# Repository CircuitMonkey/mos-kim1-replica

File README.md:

# mos-kim1-replica
MOS KIM-1 6502 replica project using CHIPz modules.

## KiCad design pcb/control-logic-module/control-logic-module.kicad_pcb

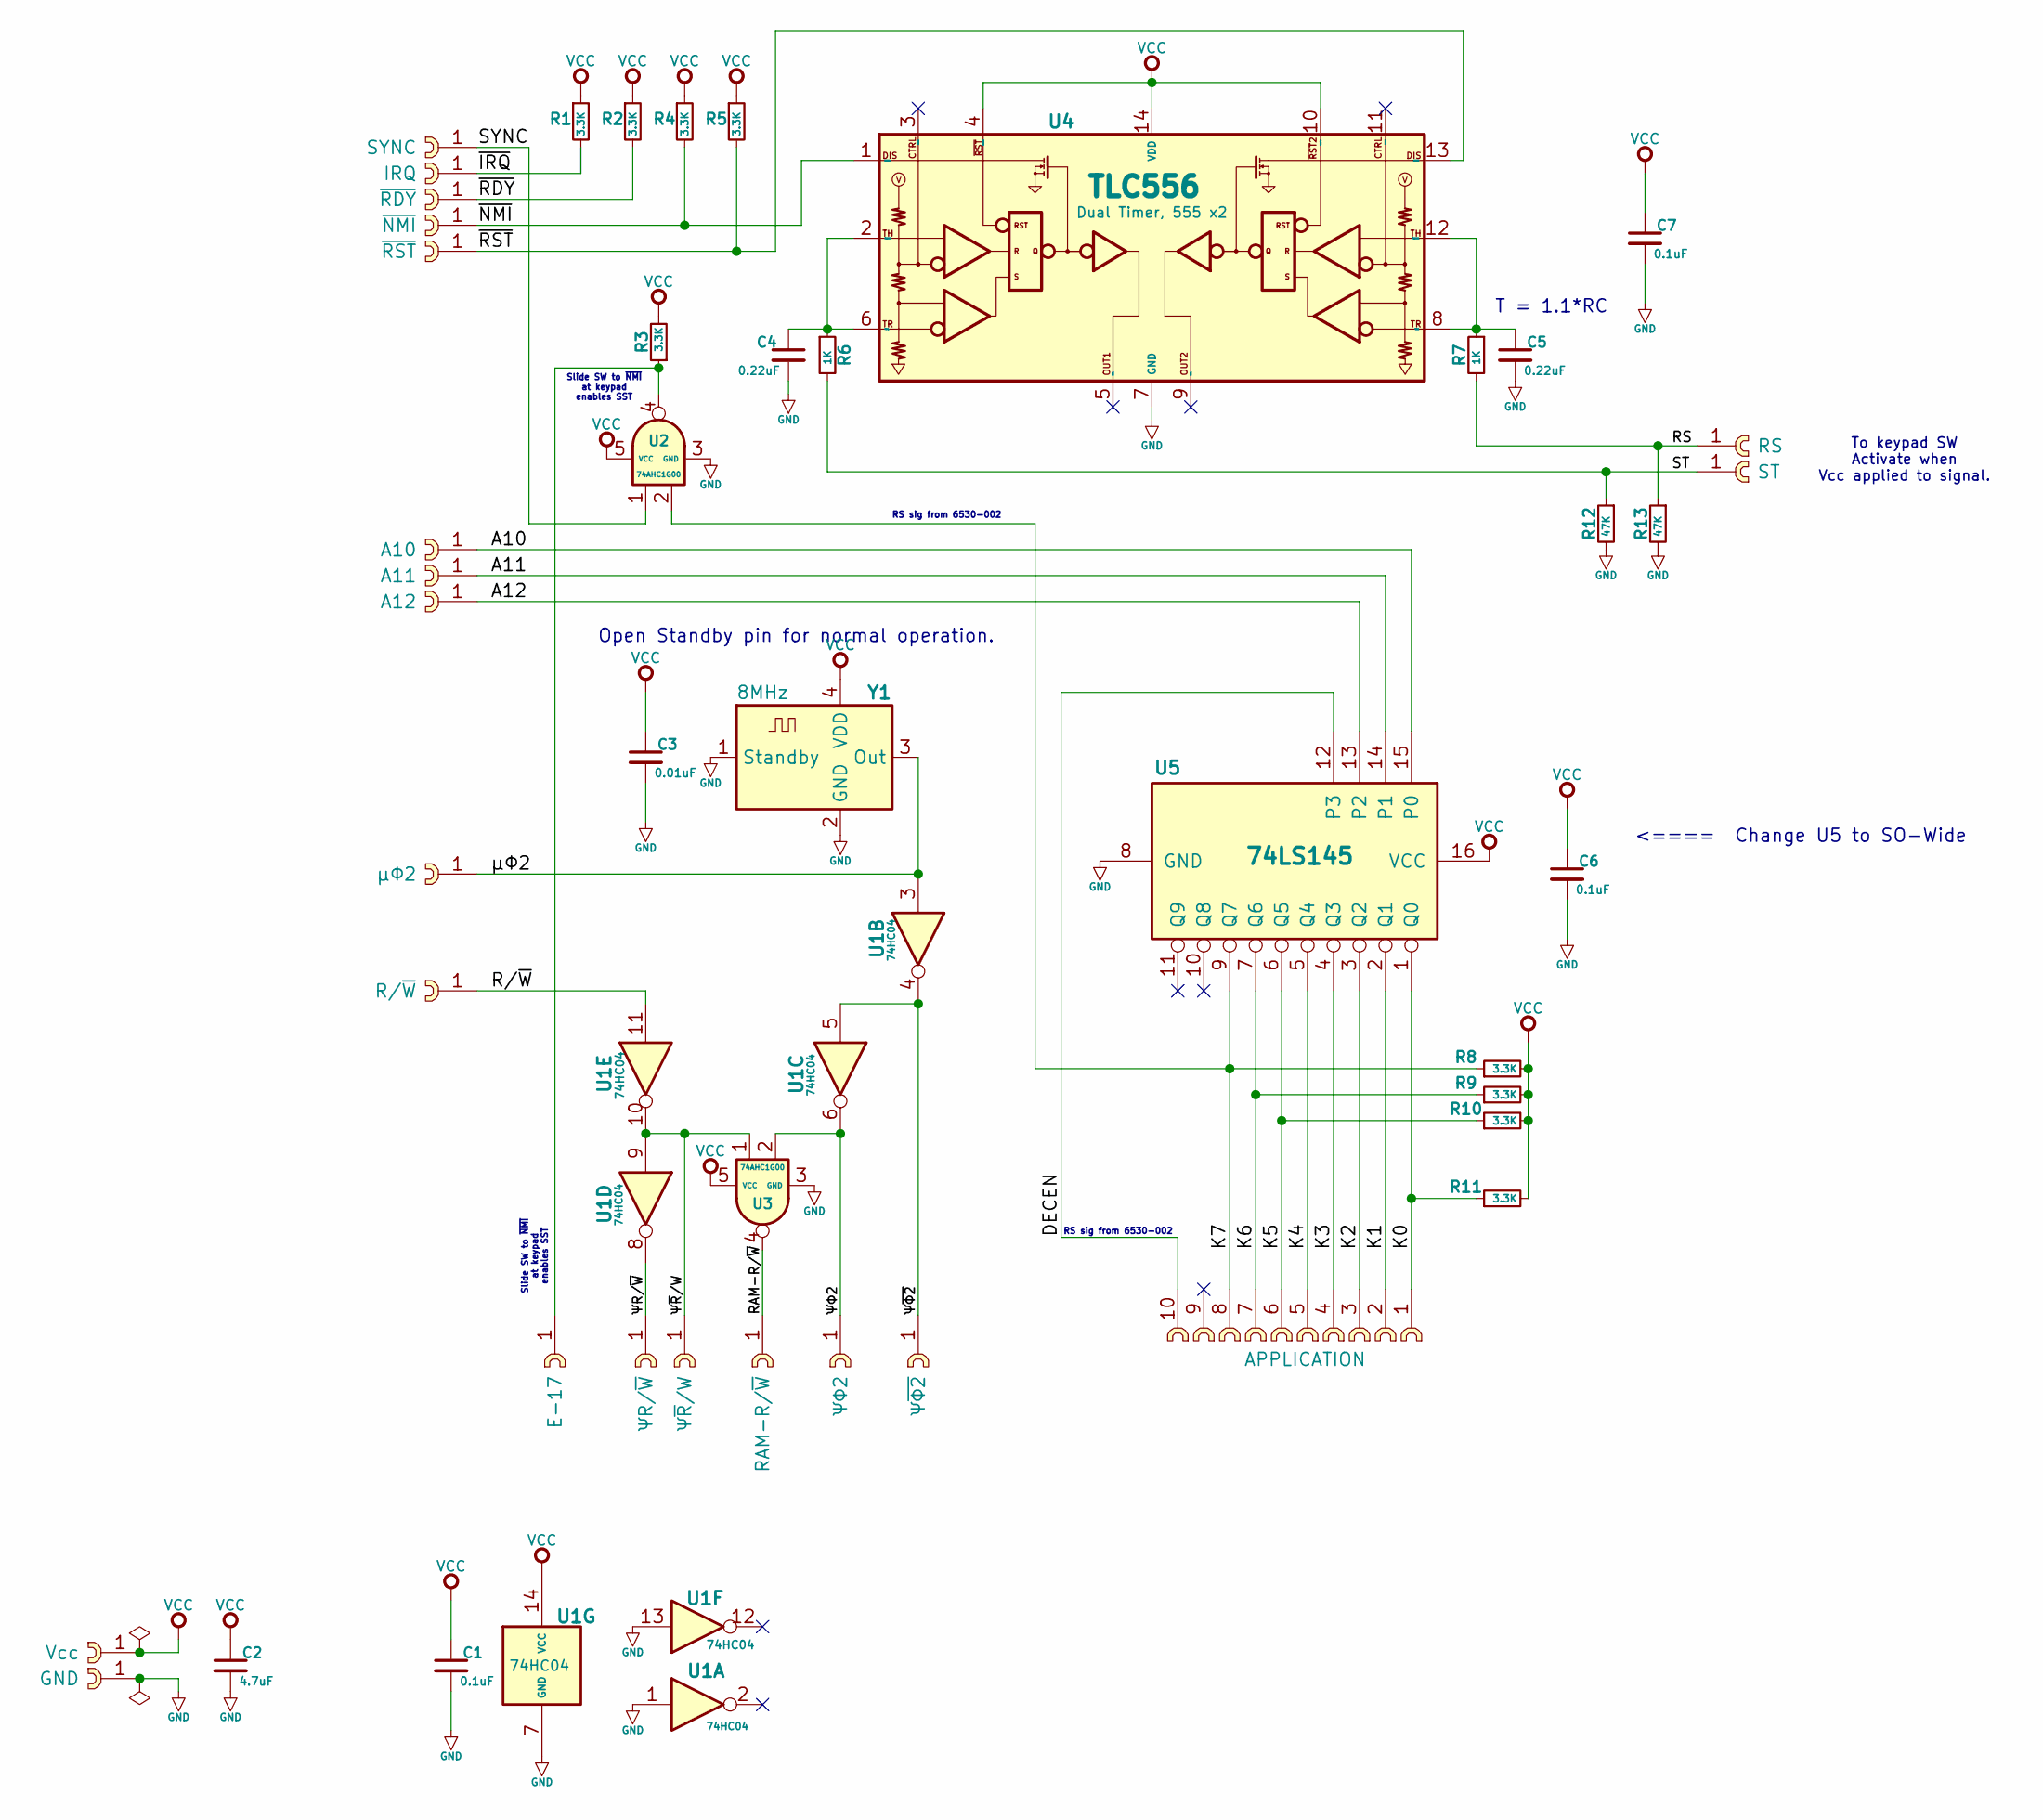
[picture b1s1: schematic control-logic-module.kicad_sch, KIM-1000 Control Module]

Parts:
C1, C6, C7: 0.1uF; C_0603_1608Metric
C2: 4.7uF; C_0603_1608Metric
C3: 0.01uF; C_0603_1608Metric
C4, C5: 0.22uF; C_0603_1608Metric
CST1: Vcc; cast-2.0-01P
CST2: GND; cast-2.0-01P
CST3: SYNC; cast-2.0-01P
CST4: IRQ; cast-2.0-01P
CST5: ~{RDY}; cast-2.0-01P
CST6: ~{NMI}; cast-2.0-01P
CST7: ~{RST}; cast-2.0-01P
CST8: A10; cast-2.0-01P
CST9: A11; cast-2.0-01P
CST10: A12; cast-2.0-01P
CST11: μΦ2; cast-2.0-01P
CST12: R/~{W}; cast-2.0-01P
CST13: E-17; cast-2.0-01P
CST14: ΨR/~{W}; cast-2.0-01P
CST15: Ψ~{R}/W; cast-2.0-01P
CST16: RAM-R/~{W}; cast-2.0-01P
CST17: ΨΦ2; cast-2.0-01P
CST18: Ψ~{Φ2}; cast-2.0-01P
CST19: APPLICATION; cast-2.0-10P
CST20: RS; cast-2.0-01P
CST21: ST; cast-2.0-01P
R1, R2, R3, R4, R5, R8, R9, R10, R11: 3.3K; R_0603_1608Metric
R6, R7: 1K; R_0603_1608Metric
R12, R13: 47K; R_0603_1608Metric
U1: 74HC04; QFN-14_EP_2.5x3_Pitch0.5mm
U2, U3: 74AHC1G00; SOT-353_SC-70-5; MPN MC74HC1G00DFT1G
U4: TLC556; SO-14_3.9x8.65mm_P1.27mm
U5: 74LS145; SO-16_3.9x9.9mm_P1.27mm
Y1: 8MHz; Oscillator_SMD_Abracon_ASDMB-4Pin_2.5x2.0mm; MPN ASD-8.000MHZ-LC-T

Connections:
/A10: CST8.1, U5.15 (P0)
/A11: CST9.1, U5.14 (P1)
/A12: CST10.1, U5.13 (P2)
/DECEN: CST19.10, U5.12 (P3)
/K0: CST19.1, R11.1, U5.1 (Q0)
/K1: CST19.2, U5.2 (Q1)
/K2: CST19.3, U5.3 (Q2)
/K3: CST19.4, U5.4 (Q3)
/K4: CST19.5, U5.5 (Q4)
/K5: CST19.6, R10.1, U5.6 (Q5)
/K6: CST19.7, R9.1, U5.7 (Q6)
/K7: CST19.8, R8.1, U2.2, U5.9 (Q7)
/RAM-R/~W: CST16.1, U3.4
/RS: CST20.1, R7.2, R13.1
/R/~W: CST12.1, U1.11
/ST: CST21.1, R6.2, R12.1
/SYNC: CST3.1, U2.1
/~IRQ: CST4.1, R1.2
/~NMI: CST6.1, R4.2, U4.1 (DISCH1)
/~RDY: CST5.1, R2.2
/~RST: CST7.1, R5.2, U4.13 (DISCH2)
/ΨR/~W: CST14.1, U1.8
/Ψ~R/W: CST15.1, U1.9, U1.10, U3.1
/Ψ~Φ2: CST18.1, U1.4, U1.5
/ΨΦ2: CST17.1, U1.6, U3.2
/μΦ2: CST11.1, U1.3, Y1.3 (Out)
GND: C1.2, C2.2, C3.2, C4.2, C5.2, C6.2, C7.2, CST2.1, R12.2, R13.2, U1.1, U1.7 (GND), U1.13, U2.3 (GND), U3.3 (GND), U4.7 (GND), U5.8 (GND), Y1.1 (Standby), Y1.2 (GND)
unnamed: CST13.1, R3.1, U2.4
unnamed: C4.1, R6.1, U4.2 (THRESH1), U4.6 (TRIG1)
unnamed: C5.1, R7.1, U4.8 (TRIG2), U4.12 (THRESH2)
VCC: C1.1, C2.1, C3.1, C6.1, C7.1, CST1.1, R1.1, R2.1, R3.2, R4.1, R5.1, R8.2, R9.2, R10.2, R11.2, U1.14 (VCC), U2.5 (VCC), U3.5 (VCC), U4.4 (RESET1), U4.10 (RESET2), U4.14 (VDD), U5.16 (VCC), Y1.4 (VDD)

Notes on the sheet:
RS sig from 6530-002
Slide SW to ~{NMI} at keypad enables SST
T = 1.1*RC
Open Standby pin for normal operation.
To keypad SW Activate when Vcc applied to signal.
<==== Change U5 to SO-Wide

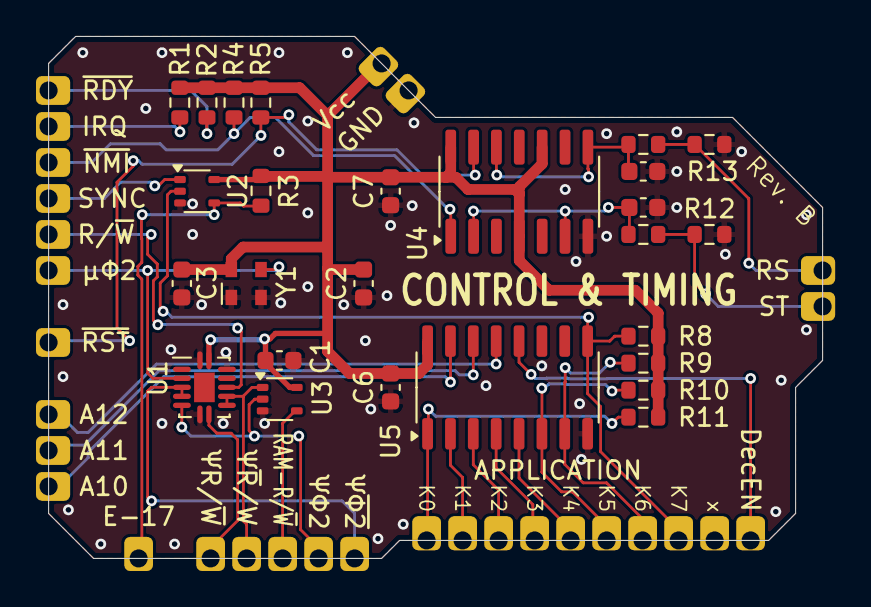
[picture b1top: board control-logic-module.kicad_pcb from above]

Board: 2 copper layers, 43.0 x 29.0 mm, 47 parts (0 on the bottom side), 31 nets.

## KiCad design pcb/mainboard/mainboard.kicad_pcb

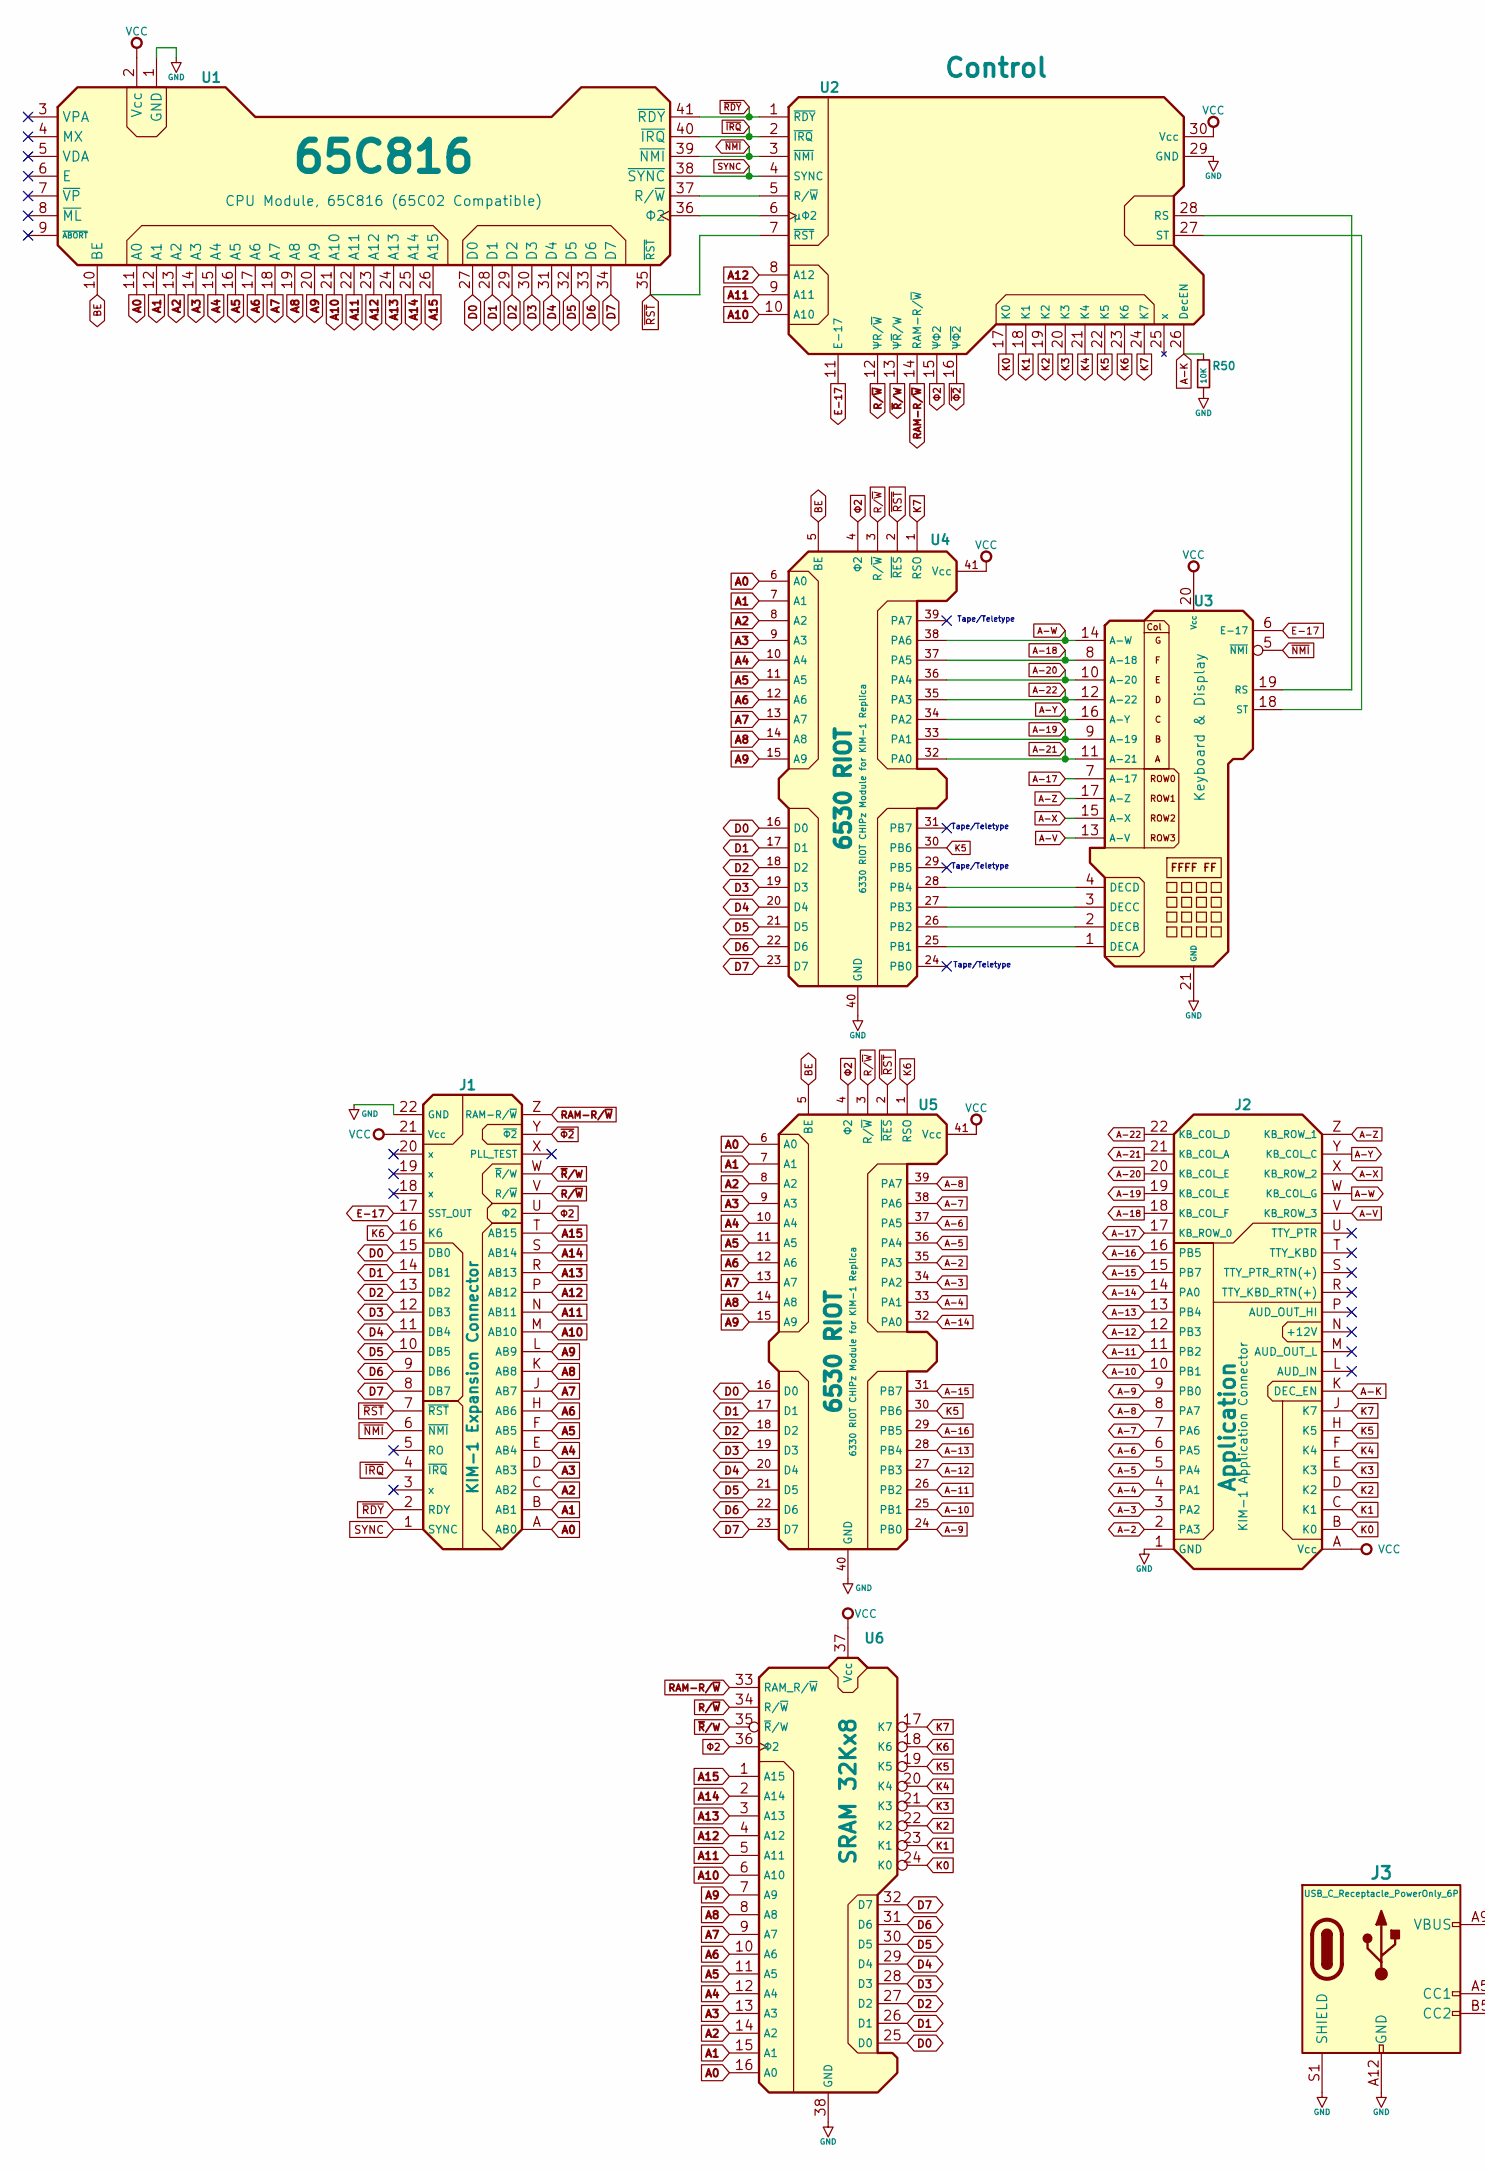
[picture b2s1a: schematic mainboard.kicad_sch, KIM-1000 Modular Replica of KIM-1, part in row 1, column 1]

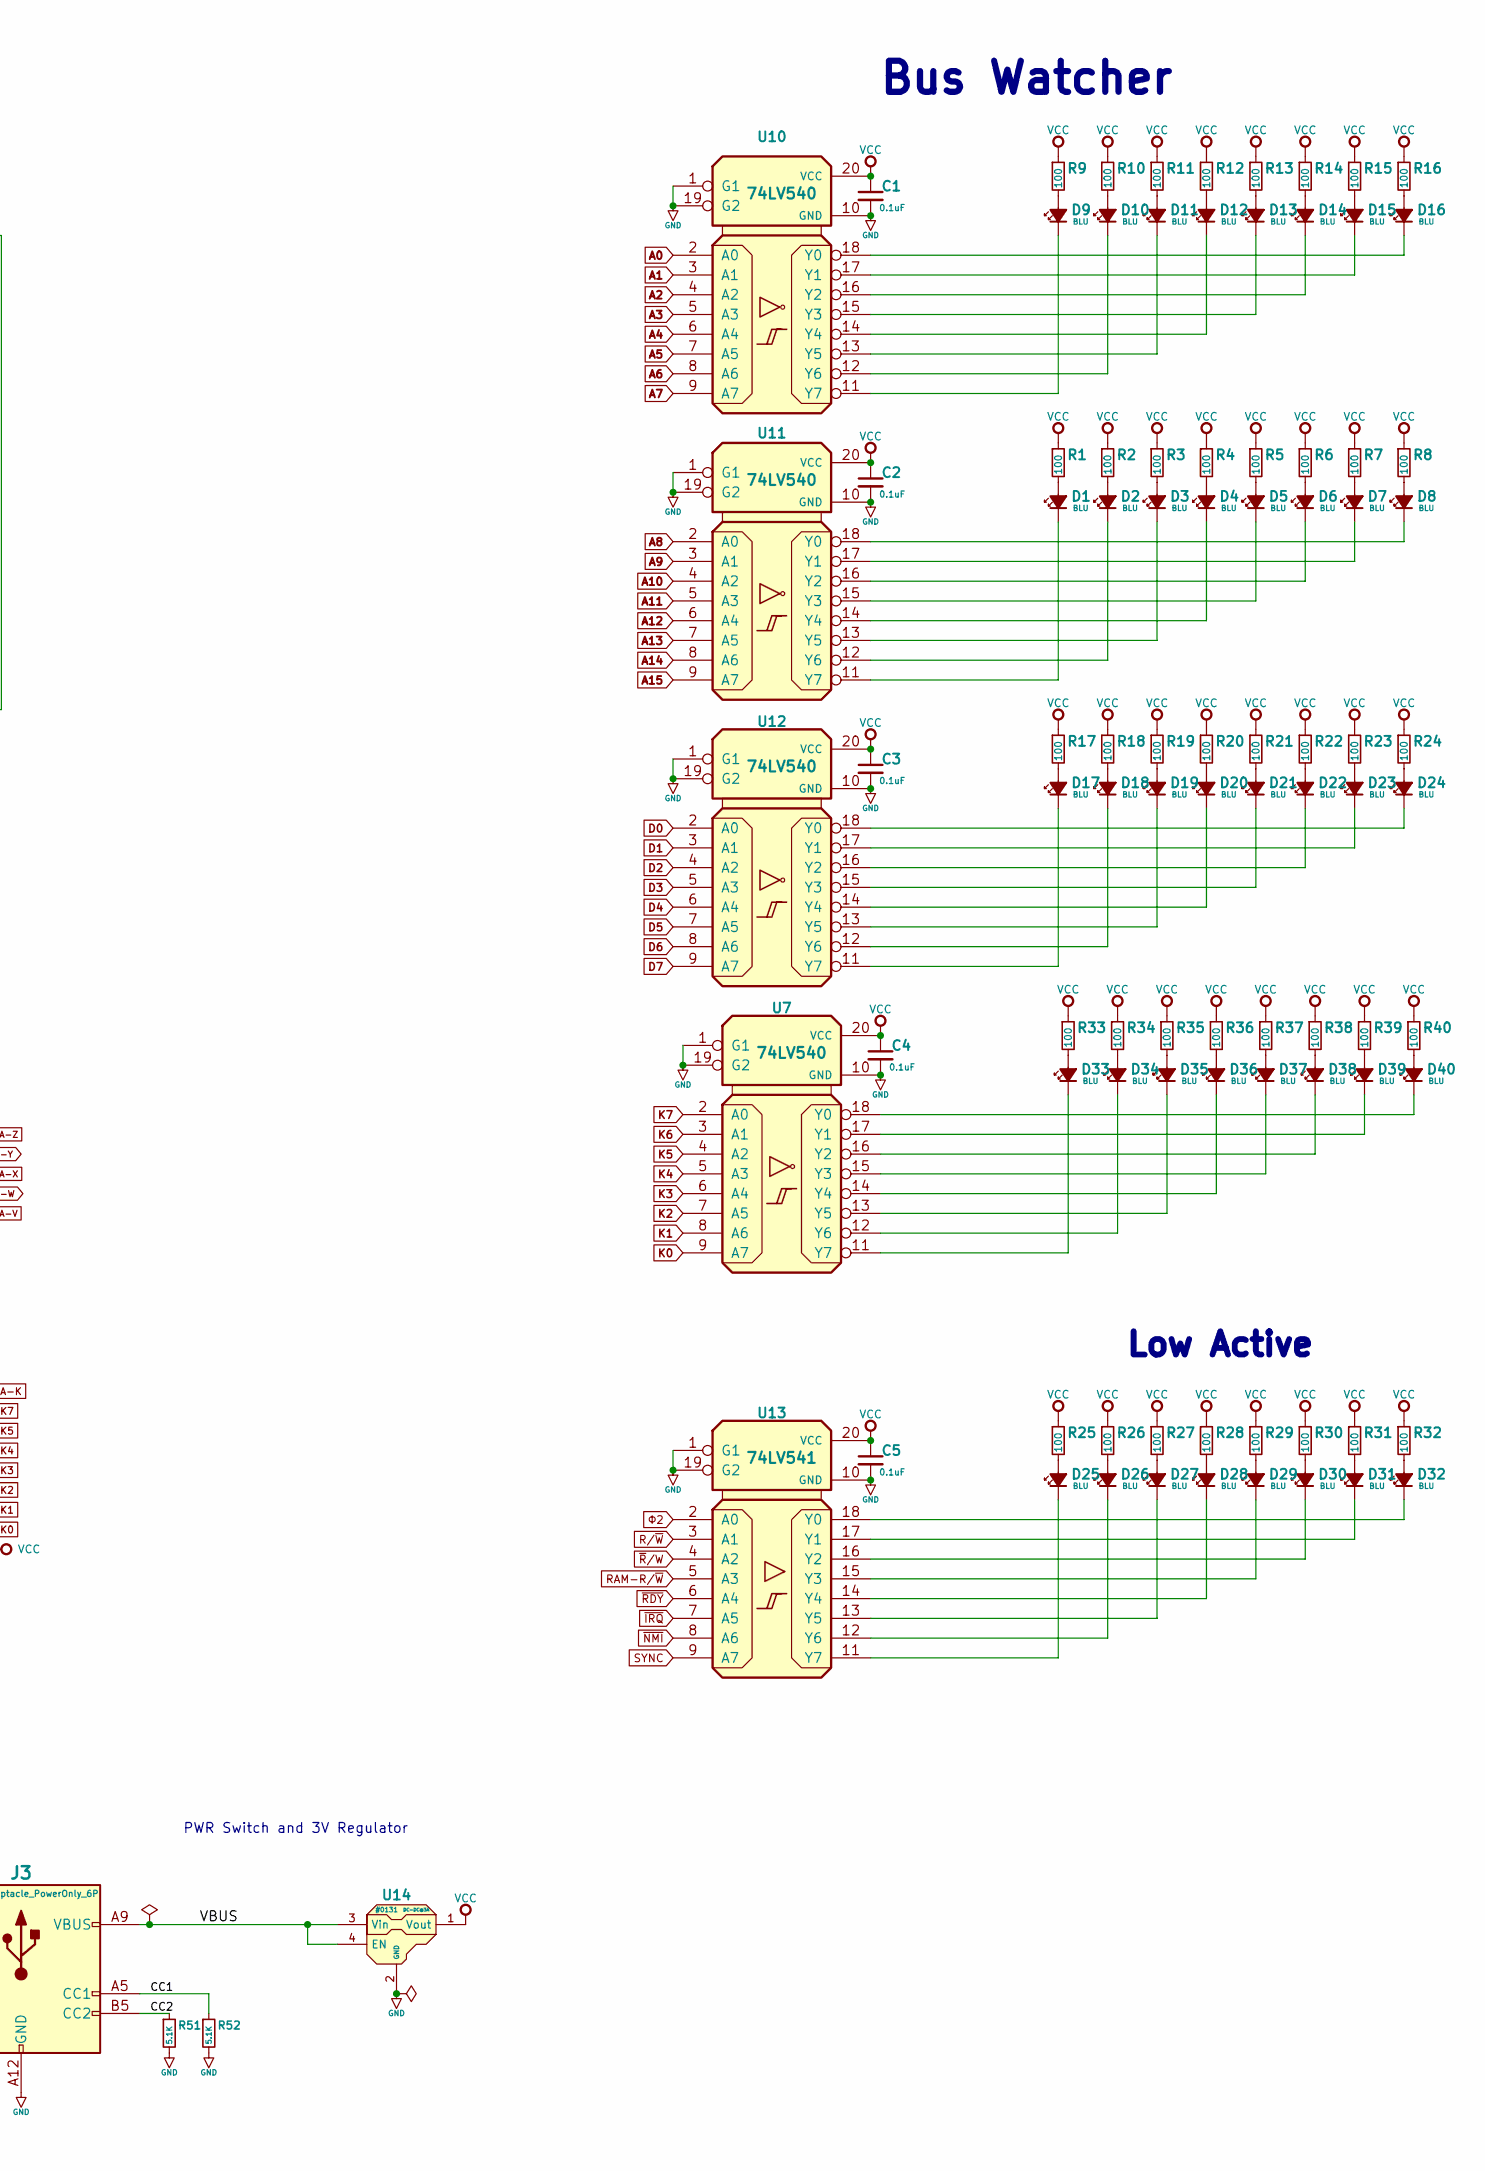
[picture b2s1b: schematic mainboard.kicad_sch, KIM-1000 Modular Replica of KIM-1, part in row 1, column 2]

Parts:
C1, C2, C3, C4, C5: 0.1uF; C_0603_1608Metric
D1, D2, D3, D4, D5, D6, D7, D8, D9, D10, D11, D12, D13, D14, D15, D16, D17, D18, D19, D20, D21, D22, D23, D24, D25, D26, D27, D28, D29, D30, D31, D32, D33, D34, D35, D36, D37, D38, D39, D40: BLU; LED_0603_1608Metric
J1: Expansion
J2: Application; Expansion
J3: USB_C_Receptacle_PowerOnly_6P; USB_C_Receptacle_HRO_TYPE-C-31-M-17
R1, R2, R3, R4, R5, R6, R7, R8, R9, R10, R11, R12, R13, R14, R15, R16, R17, R18, R19, R20, R21, R22, R23, R24, R25, R26, R27, R28, R29, R30, R31, R32, R33, R34, R35, R36, R37, R38, R39, R40: 100; R_0603_1608Metric
R50: 10K; R_0603_1608Metric
R51, R52: 5.1K; R_0603_1608Metric
U1: 65C816; CPU_65C816_Module
U2: Control; KIM1-Control-CHIPz-Module
U3: Keyboard & Display; KIM1-Kbd-Display-Module
U4, U5: 6530 RIOT; IO_6530_RIOT
U6: SRAM 32Kx8; KIM1-CHIPz-SRAM-32Kx8
U7, U10, U11, U12: 74LV540; TI_RGY0020A-VQFN-20-Pad_3.5x4.5mm; MPN SN74LV540ARGY
U13: 74LV541; TI_RKS0020B-VQFN-20-Pad_2.5x4.5mm; MPN SN74LV540ARGY
U14: #0131; 0131-DC-DC-3A

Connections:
/CC1: J3.A5 (CC1), R52.1
/CC2: J3.B5 (CC2), R51.1
/VBUS: J3.A9 (VBUS), J3.B9 (VBUS), U14.3 (Vin), U14.4 (EN)
A0: J1.A (AB0), U1.11 (A0), U4.6 (A0), U5.6 (A0), U6.16 (A0), U10.2 (A0)
A1: J1.B (AB1), U1.12 (A1), U4.7 (A1), U5.7 (A1), U6.15 (A1), U10.3 (A1)
A2: J1.C (AB2), U1.13 (A2), U4.8 (A2), U5.8 (A2), U6.14 (A2), U10.4 (A2)
A3: J1.D (AB3), U1.14 (A3), U4.9 (A3), U5.9 (A3), U6.13 (A3), U10.5 (A3)
A4: J1.E (AB4), U1.15 (A4), U4.10 (A4), U5.10 (A4), U6.12 (A4), U10.6 (A4)
A5: J1.F (AB5), U1.16 (A5), U4.11 (A5), U5.11 (A5), U6.11 (A5), U10.7 (A5)
A6: J1.H (AB6), U1.17 (A6), U4.12 (A6), U5.12 (A6), U6.10 (A6), U10.8 (A6)
A7: J1.J (AB7), U1.18 (A7), U4.13 (A7), U5.13 (A7), U6.9 (A7), U10.9 (A7)
A8: J1.K (AB8), U1.19 (A8), U4.14 (A8), U5.14 (A8), U6.8 (A8), U11.2 (A0)
A9: J1.L (AB9), U1.20 (A9), U4.15 (A9), U5.15 (A9), U6.7 (A9), U11.3 (A1)
A10: J1.M (AB10), U1.21 (A10), U2.10 (A10), U6.6 (A10), U11.4 (A2)
A11: J1.N (AB11), U1.22 (A11), U2.9 (A11), U6.5 (A11), U11.5 (A3)
A12: J1.P (AB12), U1.23 (A12), U2.8 (A12), U6.4 (A12), U11.6 (A4)
A13: J1.R (AB13), U1.24 (A13), U6.3 (A13), U11.7 (A5)
A14: J1.S (AB14), U1.25 (A14), U6.2 (A14), U11.8 (A6)
A15: J1.T (AB15), U1.26 (A15), U6.1 (A15), U11.9 (A7)
A-2: J2.2 (PA3), U5.35 (PA3)
A-3: J2.3 (PA2), U5.34 (PA2)
A-4: J2.4 (PA1), U5.33 (PA1)
A-5: J2.5 (PA4), U5.36 (PA4)
A-6: J2.6 (PA5), U5.37 (PA5)
A-7: J2.7 (PA6), U5.38 (PA6)
A-8: J2.8 (PA7), U5.39 (PA7)
A-9: J2.9 (PB0), U5.24 (PB0)
A-10: J2.10 (PB1), U5.25 (PB1)
A-11: J2.11 (PB2), U5.26 (PB2)
A-12: J2.12 (PB3), U5.27 (PB3)
A-13: J2.13 (PB4), U5.28 (PB4)
A-14: J2.14 (PA0), U5.32 (PA0)
A-15: J2.15 (PB7), U5.31 (PB7)
A-16: J2.16 (PB5), U5.29 (PB5)
A-17: J2.17 (KB_ROW_0), U3.7 (A-17)
A-18: J2.18 (KB_COL_F), U3.8 (A-18), U4.37 (PA5)
A-19: J2.19 (KB_COL_E), U3.9 (A-19), U4.33 (PA1)
A-20: J2.20 (KB_COL_E), U3.10 (A-20), U4.36 (PA4)
A-21: J2.21 (KB_COL_A), U3.11 (A-21), U4.32 (PA0)
A-22: J2.22 (KB_COL_D), U3.12 (A-22), U4.35 (PA3)
A-K: J2.K (DEC_EN), R50.1, U2.26 (DecEN)
A-V: J2.V (KB_ROW_3), U3.13 (A-V)
A-W: J2.W (KB_COL_G), U3.14 (A-W), U4.38 (PA6)
A-X: J2.X (KB_ROW_2), U3.15 (A-X)
A-Y: J2.Y (KB_COL_C), U3.16 (A-Y), U4.34 (PA2)
A-Z: J2.Z (KB_ROW_1), U3.17 (A-Z)
BE: U1.10 (BE), U4.5 (BE), U5.5 (BE)
D0: J1.15 (DB0), U1.27 (D0), U4.16 (D0), U5.16 (D0), U6.25 (D0), U12.2 (A0)
D1: J1.14 (DB1), U1.28 (D1), U4.17 (D1), U5.17 (D1), U6.26 (D1), U12.3 (A1)
D2: J1.13 (DB2), U1.29 (D2), U4.18 (D2), U5.18 (D2), U6.27 (D2), U12.4 (A2)
D3: J1.12 (DB3), U1.30 (D3), U4.19 (D3), U5.19 (D3), U6.28 (D3), U12.5 (A3)
D4: J1.11 (DB4), U1.31 (D4), U4.20 (D4), U5.20 (D4), U6.29 (D4), U12.6 (A4)
D5: J1.10 (DB5), U1.32 (D5), U4.21 (D5), U5.21 (D5), U6.30 (D5), U12.7 (A5)
D6: J1.9 (DB6), U1.33 (D6), U4.22 (D6), U5.22 (D6), U6.31 (D6), U12.8 (A6)
D7: J1.8 (DB7), U1.34 (D7), U4.23 (D7), U5.23 (D7), U6.32 (D7), U12.9 (A7)
E-17: J1.17 (SST_OUT), U2.11 (E-17), U3.6 (E-17)
GND: C1.2, C2.2, C3.2, C4.2, C5.2, J1.22 (GND), J2.1 (GND), J3.A12 (GND), J3.B12 (GND), J3.S1 (SHIELD), R50.2, R51.2, R52.2, U1.1 (GND), U2.29 (GND), U3.21 (GND), U4.40 (GND), U5.40 (GND), U6.38 (GND), U7.1 (G1), U7.10 (GND), U7.19 (G2), U7.21 (GND), U10.1 (G1), U10.10 (GND), U10.19 (G2), U10.21 (GND), U11.1 (G1), U11.10 (GND), U11.19 (G2), U11.21 (GND), U12.1 (G1), U12.10 (GND), U12.19 (G2), U12.21 (GND), U13.1 (G1), U13.10 (GND), U13.19 (G2), U13.21 (GND), U14.2 (GND)
K0: J2.B (K0), U2.17 (K0), U6.24 (K0), U7.9 (A7)
K1: J2.C (K1), U2.18 (K1), U6.23 (K1), U7.8 (A6)
K2: J2.D (K2), U2.19 (K2), U6.22 (K2), U7.7 (A5)
K3: J2.E (K3), U2.20 (K3), U6.21 (K3), U7.6 (A4)
K4: J2.F (K4), U2.21 (K4), U6.20 (K4), U7.5 (A3)
K5: J2.H (K5), U2.22 (K5), U4.30 (PB6), U5.30 (PB6), U6.19 (K5), U7.4 (A2)
K6: J1.16 (K6), U2.23 (K6), U5.1 (RSO), U6.18 (K6), U7.3 (A1)
K7: J2.J (K7), U2.24 (K7), U4.1 (RSO), U6.17 (K7), U7.2 (A0)
unnamed: D1.2 (A), R1.2
unnamed: D1.1 (K), U11.11 (Y7)
unnamed: D2.2 (A), R2.2
unnamed: D2.1 (K), U11.12 (Y6)
unnamed: D3.2 (A), R3.2
unnamed: D3.1 (K), U11.13 (Y5)
unnamed: D4.2 (A), R4.2
unnamed: D4.1 (K), U11.14 (Y4)
unnamed: D5.2 (A), R5.2
unnamed: D5.1 (K), U11.15 (Y3)
unnamed: D6.2 (A), R6.2
unnamed: D6.1 (K), U11.16 (Y2)
unnamed: D7.2 (A), R7.2
unnamed: D7.1 (K), U11.17 (Y1)
unnamed: D8.2 (A), R8.2
unnamed: D8.1 (K), U11.18 (Y0)
unnamed: D9.2 (A), R9.2
unnamed: D9.1 (K), U10.11 (Y7)
unnamed: D10.2 (A), R10.2
unnamed: D10.1 (K), U10.12 (Y6)
unnamed: D11.2 (A), R11.2
unnamed: D11.1 (K), U10.13 (Y5)
unnamed: D12.2 (A), R12.2
unnamed: D12.1 (K), U10.14 (Y4)
unnamed: D13.2 (A), R13.2
unnamed: D13.1 (K), U10.15 (Y3)
unnamed: D14.2 (A), R14.2
unnamed: D14.1 (K), U10.16 (Y2)
unnamed: D15.2 (A), R15.2
unnamed: D15.1 (K), U10.17 (Y1)
unnamed: D16.2 (A), R16.2
unnamed: D16.1 (K), U10.18 (Y0)
unnamed: D17.2 (A), R17.2
unnamed: D17.1 (K), U12.11 (Y7)
unnamed: D18.2 (A), R18.2
unnamed: D18.1 (K), U12.12 (Y6)
unnamed: D19.2 (A), R19.2
unnamed: D19.1 (K), U12.13 (Y5)
unnamed: D20.2 (A), R20.2
unnamed: D20.1 (K), U12.14 (Y4)
unnamed: D21.2 (A), R21.2
unnamed: D21.1 (K), U12.15 (Y3)
unnamed: D22.2 (A), R22.2
unnamed: D22.1 (K), U12.16 (Y2)
unnamed: D23.2 (A), R23.2
unnamed: D23.1 (K), U12.17 (Y1)
unnamed: D24.2 (A), R24.2
unnamed: D24.1 (K), U12.18 (Y0)
unnamed: D25.2 (A), R25.2
unnamed: D25.1 (K), U13.11 (Y7)
unnamed: D26.2 (A), R26.2
unnamed: D26.1 (K), U13.12 (Y6)
unnamed: D27.2 (A), R27.2
unnamed: D27.1 (K), U13.13 (Y5)
unnamed: D28.2 (A), R28.2
unnamed: D28.1 (K), U13.14 (Y4)
unnamed: D29.2 (A), R29.2
unnamed: D29.1 (K), U13.15 (Y3)
unnamed: D30.2 (A), R30.2
unnamed: D30.1 (K), U13.16 (Y2)
unnamed: D31.2 (A), R31.2
unnamed: D31.1 (K), U13.17 (Y1)
unnamed: D32.2 (A), R32.2
unnamed: D32.1 (K), U13.18 (Y0)
unnamed: D33.2 (A), R33.2
unnamed: D33.1 (K), U7.11 (Y7)
unnamed: D34.2 (A), R34.2
unnamed: D34.1 (K), U7.12 (Y6)
unnamed: D35.2 (A), R35.2
unnamed: D35.1 (K), U7.13 (Y5)
unnamed: D36.2 (A), R36.2
unnamed: D36.1 (K), U7.14 (Y4)
unnamed: D37.2 (A), R37.2
unnamed: D37.1 (K), U7.15 (Y3)
unnamed: D38.2 (A), R38.2
unnamed: D38.1 (K), U7.16 (Y2)
unnamed: D39.2 (A), R39.2
unnamed: D39.1 (K), U7.17 (Y1)
unnamed: D40.2 (A), R40.2
unnamed: D40.1 (K), U7.18 (Y0)
unnamed: U1.37 (R/~W), U2.5 (R/~W)
unnamed: U1.36 (Φ2), U2.6 (μΦ2)
unnamed: U2.28 (RS), U3.19 (RS)
unnamed: U2.27 (ST), U3.18 (ST)
unnamed: U3.1 (DECA), U4.25 (PB1)
unnamed: U3.2 (DECB), U4.26 (PB2)
unnamed: U3.3 (DECC), U4.27 (PB3)
unnamed: U3.4 (DECD), U4.28 (PB4)
RAM-R/~W: J1.Z (RAM-R/~W), U2.14 (RAM-R/~W), U6.33 (RAM_R/~W), U13.5 (A3)
R/~W: J1.V (R/~W), U2.12 (ΨR/~W), U4.3 (R/~W), U5.3 (R/~W), U6.34 (R/~W), U13.3 (A1)
SYNC: J1.1 (SYNC), U1.38 (~SYNC), U2.4 (SYNC), U13.9 (A7)
VCC: C1.1, C2.1, C3.1, C4.1, C5.1, J1.21 (Vcc), J2.A (Vcc), R1.1, R2.1, R3.1, R4.1, R5.1, R6.1, R7.1, R8.1, R9.1, R10.1, R11.1, R12.1, R13.1, R14.1, R15.1, R16.1, R17.1, R18.1, R19.1, R20.1, R21.1, R22.1, R23.1, R24.1, R25.1, R26.1, R27.1, R28.1, R29.1, R30.1, R31.1, R32.1, R33.1, R34.1, R35.1, R36.1, R37.1, R38.1, R39.1, R40.1, U1.2 (Vcc), U2.30 (Vcc), U3.20 (Vcc), U4.41 (Vcc), U5.41 (Vcc), U6.37 (Vcc), U7.20 (VCC), U10.20 (VCC), U11.20 (VCC), U12.20 (VCC), U13.20 (VCC), U14.1 (Vout)
~IRQ: J1.4 (~IRQ), U1.40 (~IRQ), U2.2 (~IRQ), U13.7 (A5)
~NMI: J1.6 (~NMI), U1.39 (~NMI), U2.3 (~NMI), U3.5 (~NMI), U13.8 (A6)
~RDY: J1.2 (RDY), U1.41 (~RDY), U2.1 (~RDY), U13.6 (A4)
~RST: J1.7 (~RST), U1.35 (~RST), U2.7 (~RST), U4.2 (~RES), U5.2 (~RES)
~R/W: J1.W (~R/W), U2.13 (Ψ~R/W), U6.35 (~R/W), U13.4 (A2)
~Φ2: J1.Y (~Φ2), U2.16 (Ψ~Φ2)
Φ2: J1.U (Φ2), U2.15 (ΨΦ2), U4.4 (Φ2), U5.4 (Φ2), U6.36 (Φ2), U13.2 (A0)

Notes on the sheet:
PWR Switch and 3V Regulator
Bus Watcher
Tape/Teletype
Low Active

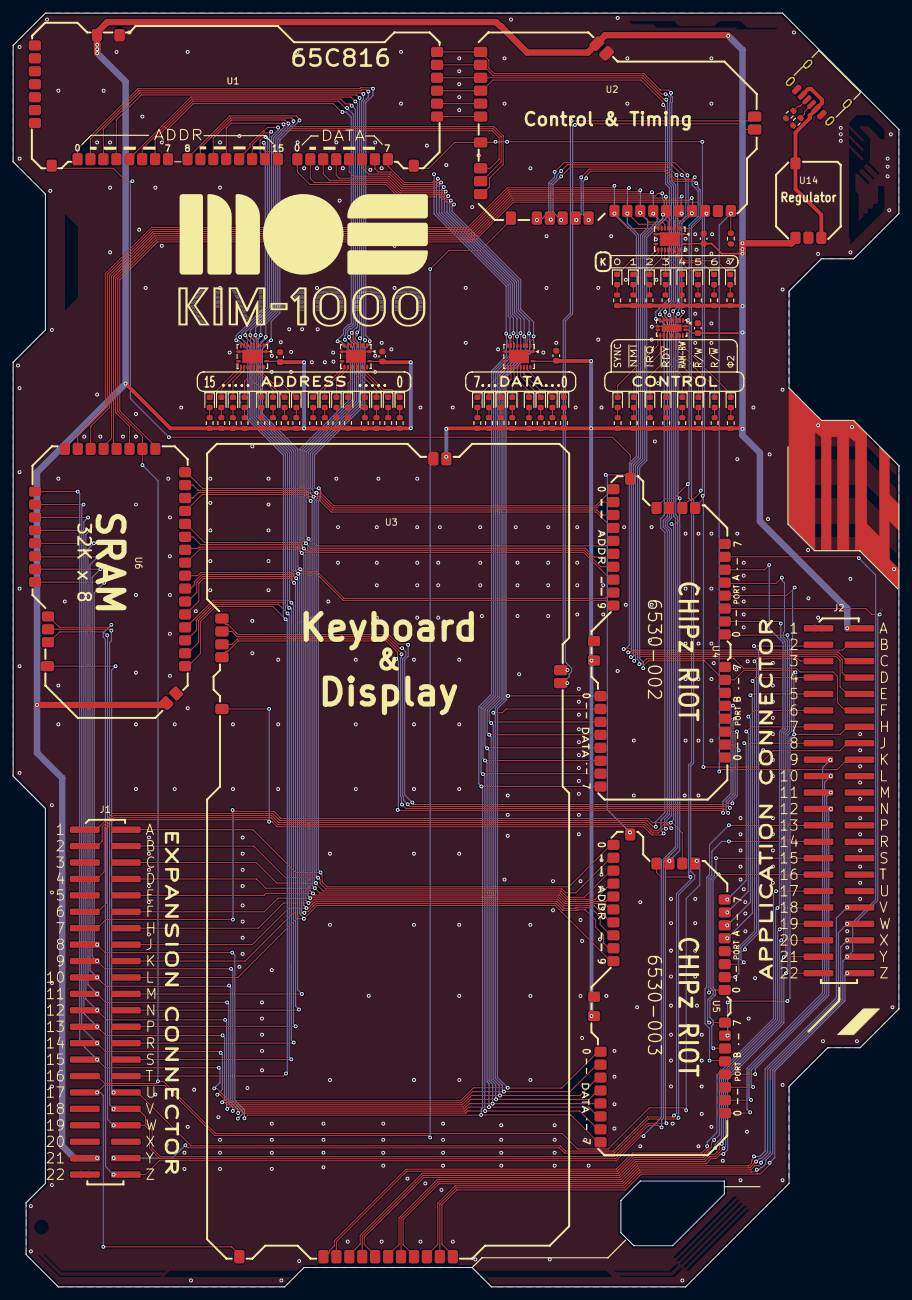
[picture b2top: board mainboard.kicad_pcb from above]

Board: 2 copper layers, 137.0 x 197.0 mm, 103 parts (0 on the bottom side), 164 nets.
